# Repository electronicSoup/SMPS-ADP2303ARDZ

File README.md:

## Synopsis

This project is an attempt at an open hardware design Switched Mode
Power Supply. It's based on the [Analog Devices
ADP2302/ADP2303](http://www.analog.com/media/en/technical-documentation/data-sheets/ADP2302_2303.pdf)
chips.

## Motivation

Basically for a design I'm working on I needed both a 5V and 3v3
rail. I have previously used another chip but found it very difficult to hand
solder, so went looking to replace my current power module. I had hoped
to find an Open Hardware design but failed to find such a thing so
started this project and documented my naivety in a [blog
post](https://www.electronicsoup.com/blog/2017/11/13/open-source-hardware/).
This project then is at present more or less a general test board for
my proposed supply. I've added Feedback resistors (R2 and R3) into the
design but I'm planning to use the fixed 5Volt 3Amp part
(ADP2303ARDZ-5.0) so I'll be using a 0 Ohm resistor for R3. In
addition as I have, in stock, a Bourns SRN6028 Inductor I've added footprints for
both that part and the, datasheet recommended, TDK VLF10040.

This project then is not much different then the [Analog
Devices](http://www.analog.com/media/en/technical-documentation/user-guides/UG-189.pdf)
but it is not a board but a KiCad Design. I'd hope that I could drag
and drop this Supply into my future designs but I somehow doubt that
it would be that simple. I sure the schematic could be brought into a
new design, which needed a supply, as an additional KiCad sheet, but
the layout would probably have to be re-done from scratch. This might
not be the case but as I've not gotten to that stage as yet.

The 3v3 rail is from a Microchip MCP1825S fixed 3v3, 500mA LDO
regulator. That part is pin compatible with the MCP1826S which is a
1Amp version, so I can easily upgrade the 3v3 Rail to 1Amp. Of course
this regulator could also be easily removed from the design, along
with it's two Caps. In addition depending on results, output efficiency
etc. I may well replace that part of the design with an improved 3v3 rail.

## Installation

Because I had to add the parts for ADP2303 and MCP1825 to the KiCad
component libraries I've had to used the latest version of KiCad,
compiled from source on my machine.

Version Info:
```
Application: kicad
Version: (2017-11-03 revision 08a9dc0)-master, debug build
Libraries:
    wxWidgets 3.0.2
    libcurl/7.47.0 GnuTLS/3.4.10 zlib/1.2.8 libidn/1.32 librtmp/2.3
Platform: Linux 4.4.0-98-generic x86_64, 64 bit, Little endian, wxGTK
Build Info:
    wxWidgets: 3.0.2 (wchar_t,wx containers,compatible with 2.8) GTK+ 2.24
    Boost: 1.58.0
    Curl: 7.47.0
    Compiler: GCC 5.4.0 with C++ ABI 1009

Build settings:
    USE_WX_GRAPHICS_CONTEXT=OFF
    USE_WX_OVERLAY=OFF
    KICAD_SCRIPTING=OFF
    KICAD_SCRIPTING_MODULES=OFF
    KICAD_SCRIPTING_WXPYTHON=OFF
    KICAD_SCRIPTING_ACTION_MENU=OFF
    BUILD_GITHUB_PLUGIN=ON
    KICAD_USE_OCE=OFF
    KICAD_SPICE=OFF
```

## License

[CERN OHL version 1.2](https://www.ohwr.org/documents/294)

First version one input Cap 10uF No Output Cap

Second Version One input Cap 10uF

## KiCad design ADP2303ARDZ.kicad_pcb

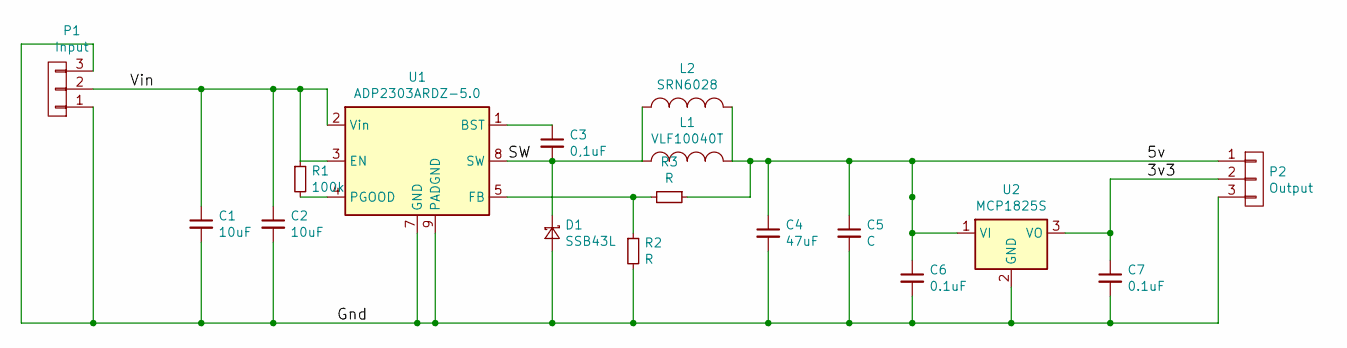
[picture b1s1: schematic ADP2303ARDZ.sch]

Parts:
C1, C2: 10uF; C_0603_1608Metric
C3: 0,1uF; C_0603_1608Metric
C4: 47uF; C_0805_2012Metric
C5: C; C_0805_2012Metric
C6, C7: 0.1uF; C_0603_1608Metric
D1: SSB43L; D_SMB_Handsoldering
L1: VLF10040T; L_TDK_VLF10040
L2: SRN6028; L_Bourns-SRN6028
P1: Input; PinSocket_1x03_P2.54mm_Vertical
P2: Output; PinSocket_1x03_P2.54mm_Vertical
R1: 100k; R_0603_1608Metric
R2, R3: R; R_0603_1608Metric
U1: ADP2303ARDZ-5.0; SOIC-8-1EP_3.9x4.9mm_Pitch1.27mm
U2: MCP1825S; SOT-223

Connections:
/3v3: C7.1, P2.2, U2.3 (VO)
/5v: C4.1, C5.1, C6.1, L1.2, L2.2, P2.1, R3.1, U2.1 (VI)
/Gnd: C1.2, C2.2, C4.2, C5.2, C6.2, C7.2, D1.2 (A), P1.1, P1.3, P2.3, R2.2, U1.7 (GND), U1.9 (PADGND), U2.2 (GND)
/SW: C3.2, D1.1 (K), L1.1, L2.1, U1.8 (SW)
/Vin: C1.1, C2.1, P1.2, R1.1, U1.2 (Vin), U1.3 (EN)
unnamed: C3.1, U1.1 (BST)
unnamed: R1.2, U1.4 (PGOOD)
unnamed: R2.1, R3.2, U1.5 (FB)

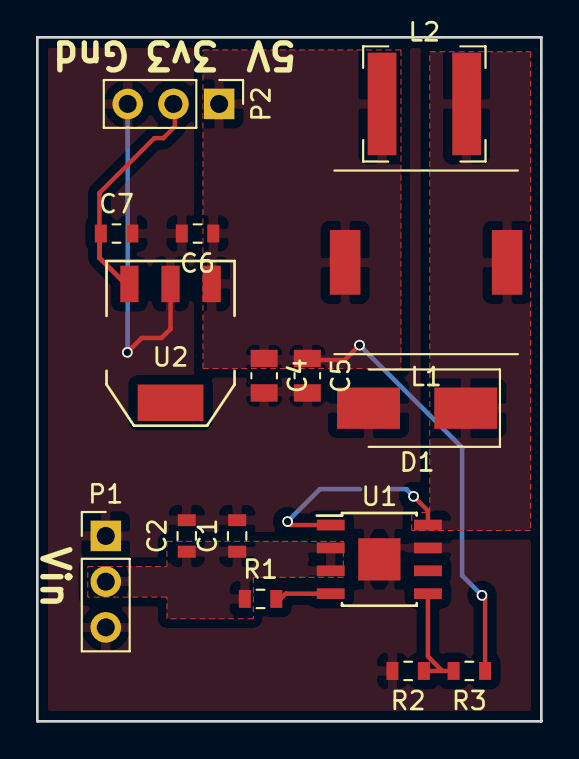
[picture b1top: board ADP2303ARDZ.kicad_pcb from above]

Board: 2 copper layers, 28.0 x 38.0 mm, 17 parts (1 on the bottom side), 8 nets.

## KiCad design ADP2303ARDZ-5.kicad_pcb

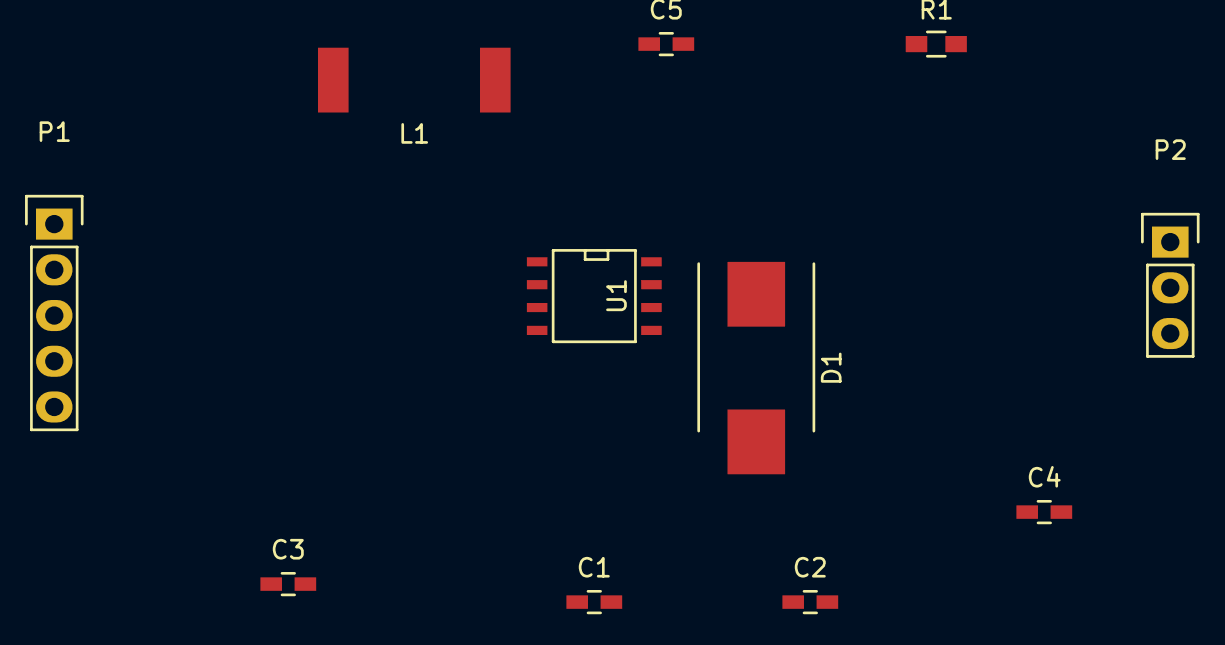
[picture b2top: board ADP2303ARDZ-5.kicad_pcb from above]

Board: 2 copper layers, 11 parts (0 on the bottom side), 6 nets, no tracks yet.

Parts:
C1, C2: 10uF; C_0603_HandSoldering
C3: 0.1uF; C_0603_HandSoldering
C4: 47uF; C_0603_HandSoldering
C5: C_Small; C_0603_HandSoldering
D1: SSB43L; DO-214AB_Handsoldering
L1: VLF10040T-4R7N5R4; VLF10040_Inductor
P1: CONN_01X05; Pin_Header_Straight_1x05
P2: CONN_01X03; Pin_Header_Straight_1x03
R1: 100k; R_0603_HandSoldering
U1: ADP2303ARDZ; SOIC-8-N

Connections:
/Gnd: C1.1, C2.1, C4.2, C5.2, D1.2, P1.1, P1.2, P1.4, P1.5, P2.3, U1.7
/Vin: C1.2, C2.2, P1.3, R1.1, U1.2, U1.3
/Vout: C4.1, C5.1, L1.2, P2.1, U1.5
unnamed: C3.1, U1.1
unnamed: C3.2, D1.1, L1.1, U1.8
unnamed: R1.2, U1.4

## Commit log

2017-10-25 Initial commit of the project
2017-10-25 Added electronicSoup schematic library to the project
2017-10-25 Finished the schematic layout
2017-10-25 Created the board file but not laid out as yet.
2017-10-30 Added the dc-dc converters to the official kicad library
    Forked the kicad-libraries github project and added the ADP230x and MCP1825s and used both components in this design
2017-11-11 moved to v5 footprints so a few missing
2017-11-11 Added feedback resistors so adjustable version could be used.
2017-11-13 Changed the name of the project, to a more genearl name
2017-11-13 Changed design to use local componenet libs
2017-11-13 Added a local directory of footprints
2017-11-13 Added SOIC-8 and SOT-223 to local footprints
2017-11-13 Selected local footprints for the design
2017-11-13 Added value for diode
2017-11-15 rough layout
2017-11-15 Added Readme file to project
2017-11-15 Added a LICENSE. Cern OHL
2017-11-15 attempt to propertly display version info
2017-11-15 corrected orientation of Inductors
2017-11-15 Fully connected but no Gnd plane as yet
2017-12-18 Added 0805 Cap Footprint
2017-12-18 Change layout to use 0805 Cap
